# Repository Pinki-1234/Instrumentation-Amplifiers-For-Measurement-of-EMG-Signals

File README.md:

# Instrumentation Amplifiers for Measurement of EMG Signals

## Overview
This project focuses on designing and building an **Instrumentation Amplifier Circuit** specifically for measuring **Electromyography (EMG)** signals.  
The EMG signal is a bioelectrical signal produced by skeletal muscles, generally spanning **0.1 mV–5 mV** in amplitude and occupying a frequency range of **0–500 Hz**.  
To accurately capture and amplify this low-frequency, low-amplitude signal, the circuit design integrates both **high CMRR instrumentation amplification** and **selective bandpass filtering**, ensuring minimal noise interference and maximum fidelity.

---

## Objectives
- To design a **low-noise instrumentation amplifier** for biomedical EMG signal acquisition.  
- To achieve optimal **common-mode noise rejection** and **signal integrity**.  
- To implement a **bandpass filter** that passes frequencies relevant to EMG (50–150 Hz).  
- To validate the design using circuit simulations and performance testing.

---

## Project Architecture
The system is divided into two core functional blocks:

### 1. Instrumentation Amplifier Block
- Built using a **three-op-amp configuration** based on **OP07** operational amplifiers.  
- Provides high input impedance, excellent stability, and precise gain control.  
- Achieves an experimental gain of approximately **54 V/V**, aligning closely with the expected **55 V/V** value.  
- Ensures **high CMRR**, effectively filtering out common-mode interference and power-line noise.

### 2. Bandpass Filter Block
- Implements a **6th-order active bandpass filter** with a passband between **50 Hz and 250 Hz**.  
- Designed to preserve the EMG signal energy (primarily in 50–150 Hz) while blocking unwanted components.  
- Demonstrated strong attenuation of frequencies at **20 Hz** and **1 kHz**, confirming the filter’s effective roll-off characteristics.

---

## Circuit Design and Components
The project employs through-hole components, structured using **KiCad PCB Design Tools**.

### Key Components
- **ICs:** OP07 (x7)  
- **Resistors:** Ranging between 1 kΩ to 680 kΩ  
- **Capacitors:** 2.2 nF to 10 µF (radial THT)  
- **Connectors:** 2.54 mm pitch sockets for input/output  
- **Power Supply:** ±12 V DC dual supply  

### Tools Used
- **Simulation:** Tektronix TBS1072B Digital Oscilloscope  
- **PCB Design:** KiCad (schematic capture, footprint assignment, ERC, DRC)  
- **3D Visualization:** KiCad 3D Model View  

---

## Results and Testing

### Instrumentation Amplifier Testing:
- **Input:** 2 mV (differential, 180° out of phase)  
- **Output:** 216 mV  
- **Gain:** ~54 V/V (validated via oscilloscope readings)

### Filter Testing:
- **Input:** 100 mV sine wave at various frequencies  
- **20 Hz →** Output attenuated heavily  
- **100 Hz →** Signal passed cleanly  
- **1 kHz →** Output significantly reduced  

This confirms the amplifier–filter chain delivers the desired selective response and accuracy for EMG signal acquisition.

---

## PCB Design
The PCB was designed for compactness and low interference:

- **Schematic Capture:** Completed with correct symbol–footprint mapping  
- **Electrical Rule Check (ERC):** No major unconnected items or design violations  
- **Design Rule Check (DRC):** Verified compliance with layout standards  
- **3D View:** Ensured precise component placement for manufacturing  

---

## Applications
- Biomedical instrumentation, specifically **EMG signal measurement**  
- Medical research and muscle activity analysis  
- Biosignal processing and human–machine interface systems  
- Educational projects for analog circuit design and bioelectronics

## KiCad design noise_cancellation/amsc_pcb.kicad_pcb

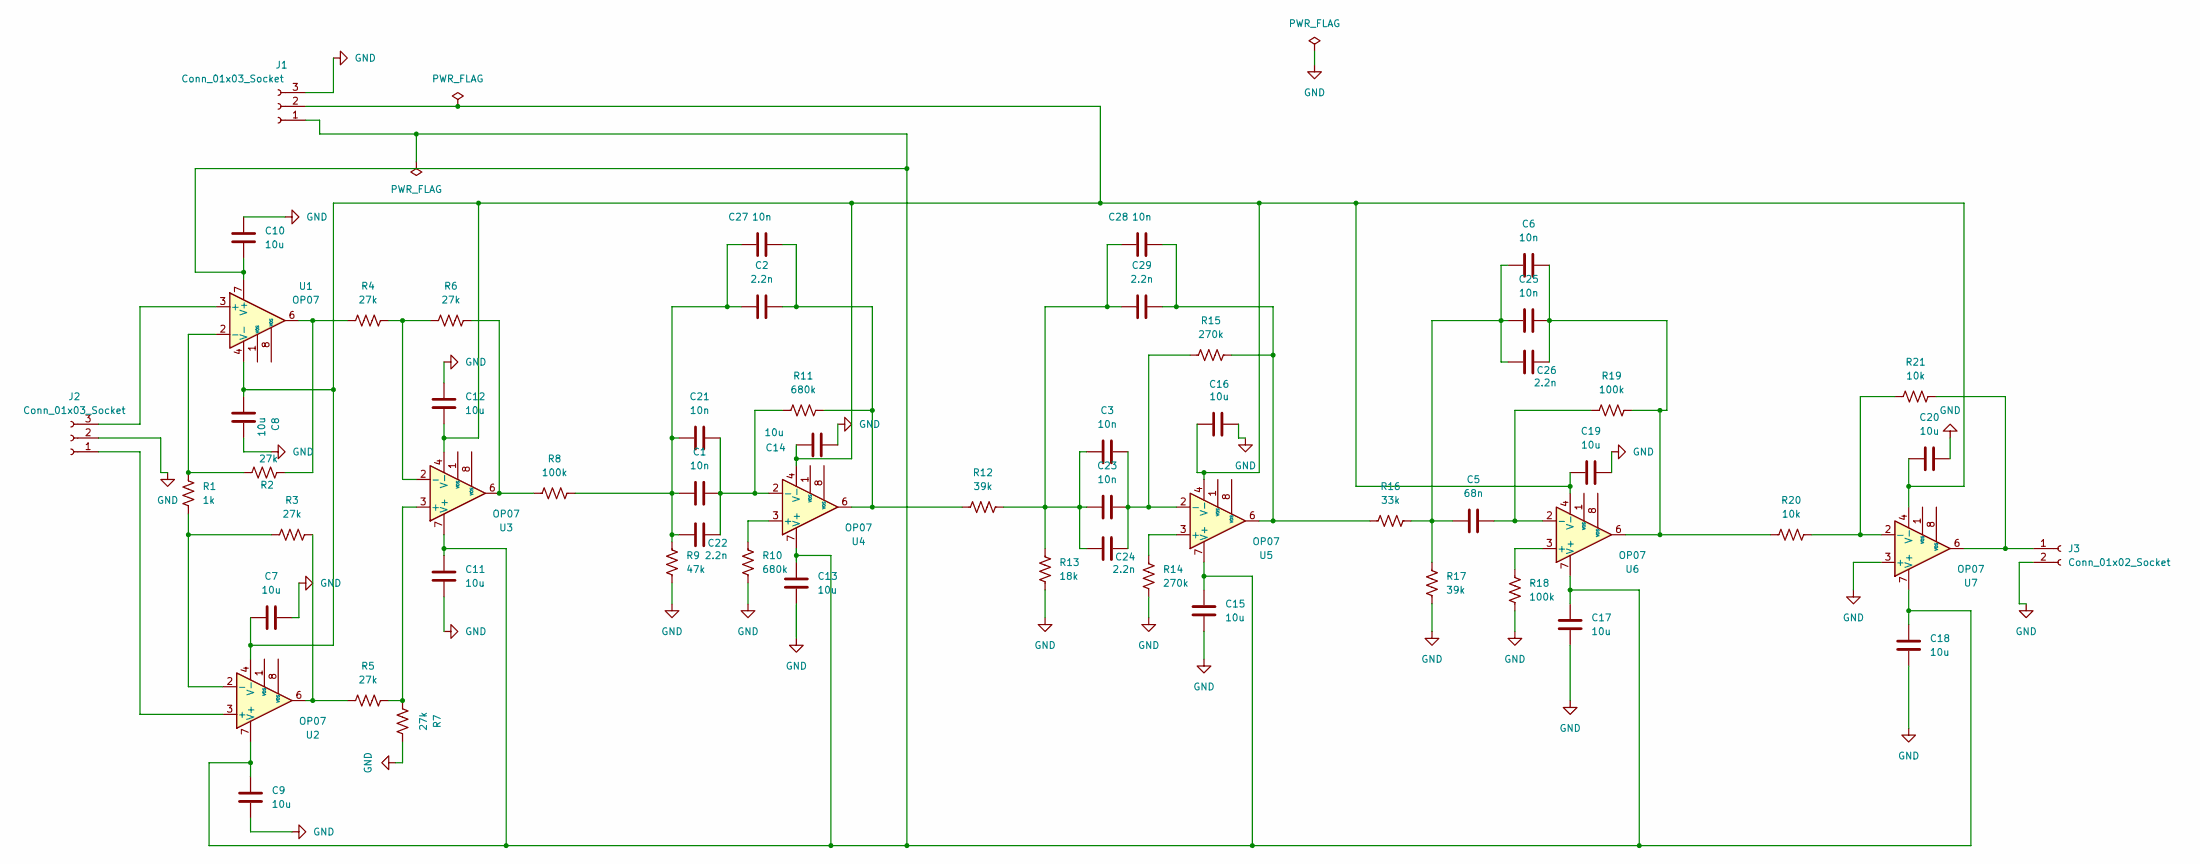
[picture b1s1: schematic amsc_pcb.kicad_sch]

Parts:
C1, C3, C6, C21, C23, C25, C27, C28: 10n; CP_Radial_D8.0mm_P3.50mm
C2, C22, C24, C26, C29: 2.2n; CP_Radial_D8.0mm_P3.50mm
C5: 68n; CP_Radial_D8.0mm_P3.50mm
C7, C8, C9, C10, C11, C12, C13, C14, C15, C16, C17, C18, C19, C20: 10u; CP_Radial_D8.0mm_P3.50mm
J1, J2: Conn_01x03_Socket; PinSocket_1x03_P2.54mm_Vertical
J3: Conn_01x02_Socket; PinSocket_1x02_P2.54mm_Vertical
R1: 1k; R_Axial_DIN0309_L9.0mm_D3.2mm_P12.70mm_Horizontal
R2, R3, R4, R5, R6, R7: 27k; R_Axial_DIN0309_L9.0mm_D3.2mm_P12.70mm_Horizontal
R8, R18, R19: 100k; R_Axial_DIN0309_L9.0mm_D3.2mm_P12.70mm_Horizontal
R9: 47k; R_Axial_DIN0309_L9.0mm_D3.2mm_P12.70mm_Horizontal
R10, R11: 680k; R_Axial_DIN0309_L9.0mm_D3.2mm_P12.70mm_Horizontal
R12, R17: 39k; R_Axial_DIN0309_L9.0mm_D3.2mm_P12.70mm_Horizontal
R13: 18k; R_Axial_DIN0309_L9.0mm_D3.2mm_P12.70mm_Horizontal
R14, R15: 270k; R_Axial_DIN0309_L9.0mm_D3.2mm_P12.70mm_Horizontal
R16: 33k; R_Axial_DIN0309_L9.0mm_D3.2mm_P12.70mm_Horizontal
R20, R21: 10k; R_Axial_DIN0309_L9.0mm_D3.2mm_P12.70mm_Horizontal
U1, U2, U3, U4, U5, U6, U7: OP07; DIP-8_W7.62mm

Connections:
GND: C7.2, C8.2, C9.2, C10.1, C11.1, C12.1, C13.2, C14.2, C15.2, C16.2, C17.2, C18.2, C19.2, C20.2, J1.3, J2.2, J3.2, R7.2, R9.2, R10.2, R13.2, R14.2, R17.2, R18.2, U7.3 (+)
unnamed: C1.1, C2.1, C21.1, C22.1, C27.1, R8.2, R9.1
unnamed: C2.2, C27.2, R11.2, R12.1, U4.6
unnamed: C3.1, C23.1, C24.1, C28.1, C29.1, R12.2, R13.1
unnamed: C5.1, C6.1, C25.1, C26.1, R16.2, R17.1
unnamed: C6.2, C25.2, C26.2, R19.2, R20.1, U6.6
unnamed: C28.2, C29.2, R15.2, R16.1, U5.6
unnamed: C9.1, C10.2, C11.2, C13.1, C15.1, C17.1, C18.1, J1.1, U1.7 (V+), U2.7 (V+), U3.7 (V+), U4.7 (V+), U5.7 (V+), U6.7 (V+), U7.7 (V+)
unnamed: C7.1, C8.1, C12.2, C14.1, C16.1, C19.1, C20.1, J1.2, U1.4 (V-), U2.4 (V-), U3.4 (V-), U4.4 (V-), U5.4 (V-), U6.4 (V-), U7.4 (V-)
unnamed: J2.1, U2.3 (+)
unnamed: J2.3, U1.3 (+)
unnamed: J3.1, R21.2, U7.6
unnamed: R2.2, R4.1, U1.6
unnamed: R3.2, R5.1, U2.6
unnamed: R6.2, R8.1, U3.6
unnamed: R1.1, R2.1, U1.2 (-)
unnamed: R1.2, R3.1, U2.2 (-)
unnamed: R5.2, R7.1, U3.3 (+)
unnamed: R4.2, R6.1, U3.2 (-)
unnamed: R10.1, U4.3 (+)
unnamed: C1.2, C21.2, C22.2, R11.1, U4.2 (-)
unnamed: R14.1, U5.3 (+)
unnamed: C3.2, C23.2, C24.2, R15.1, U5.2 (-)
unnamed: R18.1, U6.3 (+)
unnamed: C5.2, R19.1, U6.2 (-)
unnamed: R20.2, R21.1, U7.2 (-)

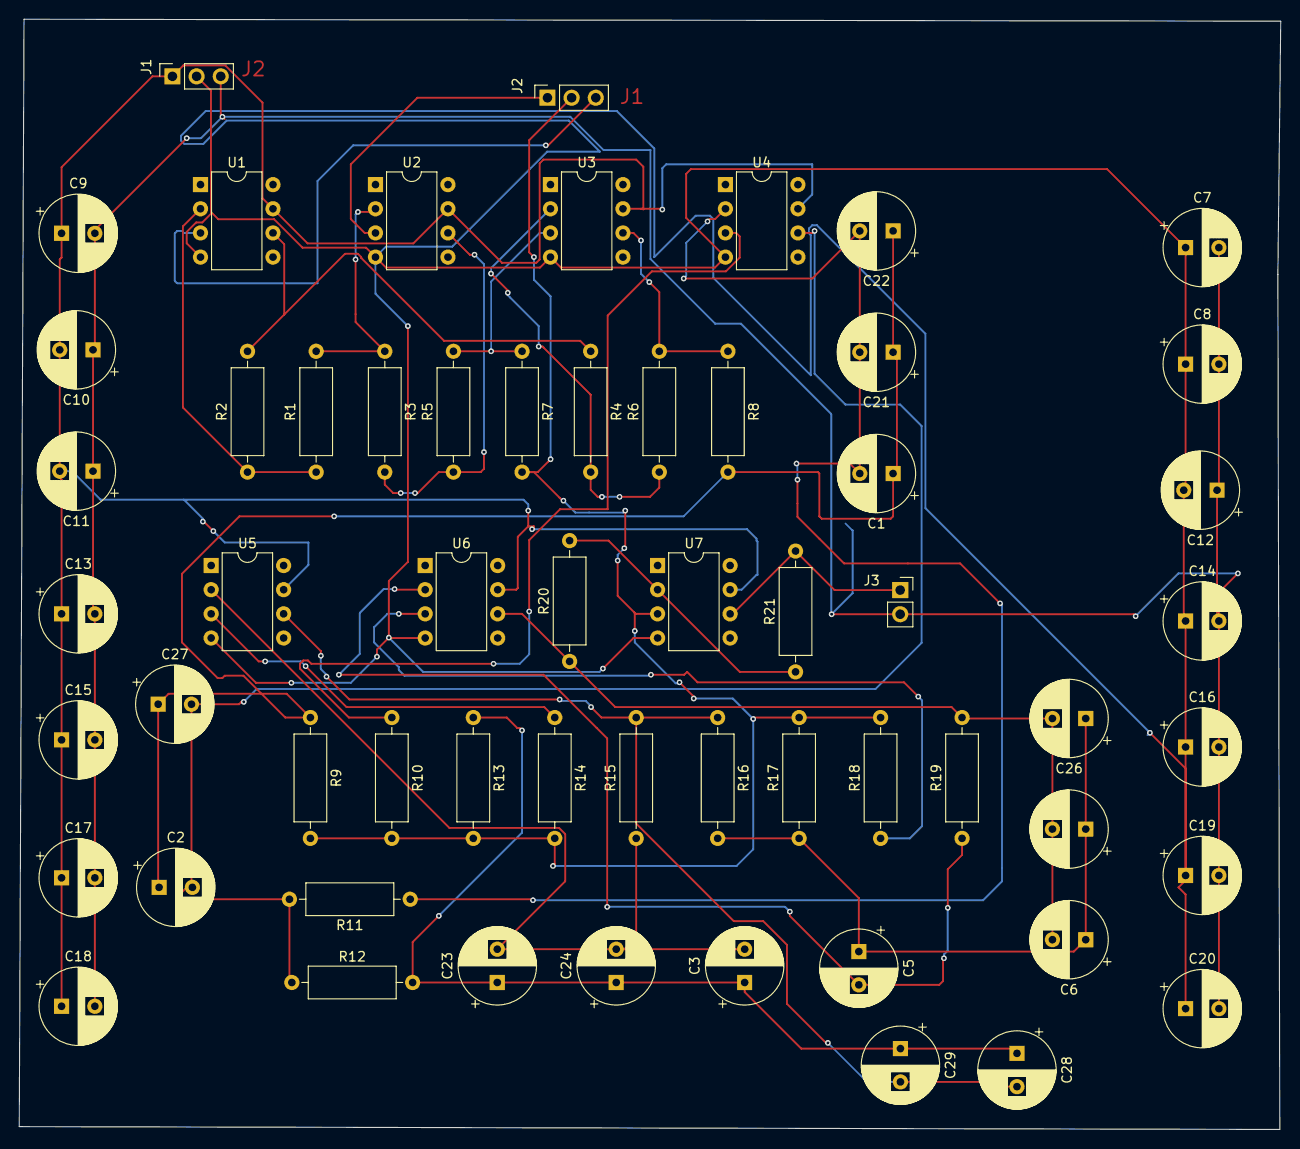
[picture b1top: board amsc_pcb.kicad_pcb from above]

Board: 2 copper layers, 132.6 x 116.7 mm, 59 parts (0 on the bottom side), 26 nets.

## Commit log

2025-10-25 added project files
